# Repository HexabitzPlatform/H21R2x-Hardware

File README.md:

# H21R20-Hardware
Hexabitz ESP32-C3 WiFi+BLE Module Hardware Design

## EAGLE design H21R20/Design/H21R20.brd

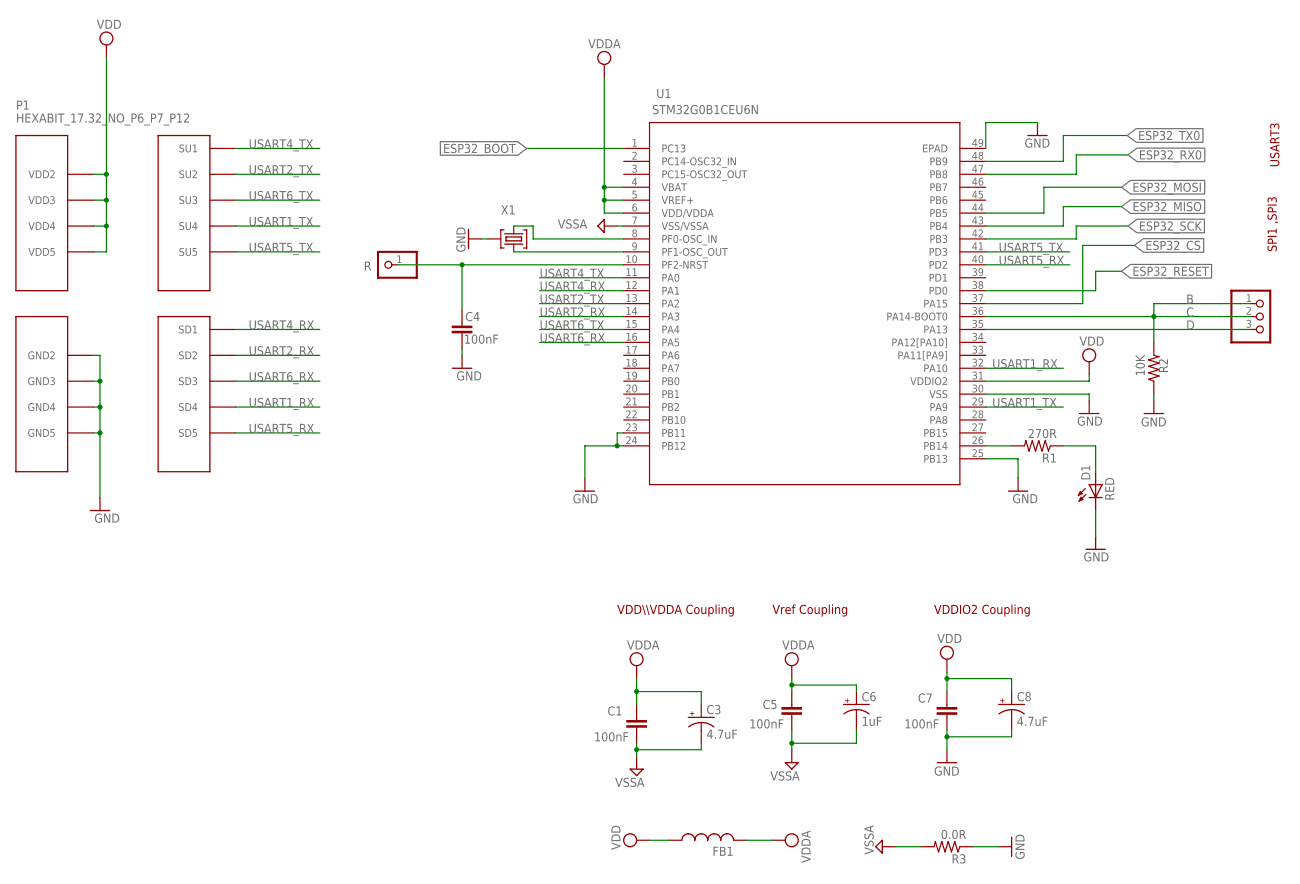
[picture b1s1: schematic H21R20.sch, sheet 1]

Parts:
C1, C5, C7: 100nF; C-0603; TOLERANCE 10%; VOLTAGE_RATING 16.0 V; MPN '0603YC104K4T2A
C3: 4.7uF; C-0805-POL; TOLERANCE 20%; VOLTAGE_RATING 10.0 V; MPN '10TPU4R7MSI
C4: 100nF; C-0603; TOLERANCE 10%; VOLTAGE_RATING 16.0 V; MPN 0603YC104K4T2A
C6: 1uF; C-0805-POL; TOLERANCE 20%; VOLTAGE_RATING 10.0 V; MPN 'CC0805KKX7R7BB105
C8: 4.7uF; C-0805-POL; TOLERANCE 10%; VOLTAGE_RATING 16.0 V; MPN '10TPU4R7MSI
D1: RED; VLMS1300-GS08
FB1: FB-TDK_MMZ1608Y300B; MPN MMZ1608Y300BTA00
JP1: PINHD-1X3; 1X03
P1: HEXABIT_17.32_NO_P6_P7_P12
R: PINHD-1X1; 1X01
R1: 270R; R-0603; MPN 'ERJ-3GEYJ271V
R2: 10K; R-0603; MPN '060300J0103T5E
R3: 0.0R; R-0603; MPN RC0603JR-070RL
U1: STM32G0B1CEU6N; HEXABITZ_ICS_QFN_B1CEU6_STM-L
X1: 8MHZ; XTALL_CSTCE8M00G52; MPN CSTNE8M00G550000R0

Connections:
C: JP1.1, JP1.2, R2.2, U1.36 (PA14-BOOT0)
D: JP1.3, U1.35 (PA13)
ESP32_BOOT: U1.1 (PC13); also elsewhere on the board
ESP32_CS: U1.37 (PA15); also elsewhere on the board
ESP32_MISO: U1.43 (PB4); also elsewhere on the board
ESP32_MOSI: U1.44 (PB5); also elsewhere on the board
ESP32_RESET: U1.38 (PD0); also elsewhere on the board
ESP32_RX0: U1.47 (PB8); also elsewhere on the board
ESP32_SCK: U1.42 (PB3); also elsewhere on the board
ESP32_TX0: U1.48 (PB9); also elsewhere on the board
GND: C4.1, C7.1, C8.2 (-), D1.C, P1.PAD_PD8 (GND2), P1.PAD_PD9 (GND3), P1.PAD_PD10 (GND4), P1.PAD_PD11 (GND5), R2.1, R3.1, U1.23 (PB11), U1.24 (PB12), U1.25 (PB13), U1.30 (VSS), U1.49 (EPAD), X1.P$2 (2); also elsewhere on the board
unnamed: U1.8 (PF0-OSC_IN), X1.P$1 (1)
unnamed: U1.9 (PF1-OSC_OUT), X1.P$3 (3)
unnamed: C4.2, R.1, U1.10 (PF2-NRST)
unnamed: R1.2, U1.26 (PB14)
unnamed: D1.A, R1.1
USART1_RX: P1.PAD_PD4 (SD4), U1.32 (PA10)
USART1_TX: P1.PAD_PU4 (SU4), U1.29 (PA9)
USART2_RX: P1.PAD_PD2 (SD2), U1.14 (PA3)
USART2_TX: P1.PAD_PU2 (SU2), U1.13 (PA2)
USART4_RX: P1.PAD_PD1 (SD1), U1.12 (PA1)
USART4_TX: P1.PAD_PU1 (SU1), U1.11 (PA0)
USART5_RX: P1.PAD_PD5 (SD5), U1.40 (PD2)
USART5_TX: P1.PAD_PU5 (SU5), U1.41 (PD3)
USART6_RX: P1.PAD_PD3 (SD3), U1.16 (PA5)
USART6_TX: P1.PAD_PU3 (SU3), U1.15 (PA4)
VDD: C7.2, C8.1 (+), FB1.1, P1.PAD_PU8 (VDD2), P1.PAD_PU9 (VDD3), P1.PAD_PU10 (VDD4), P1.PAD_PU11 (VDD5), U1.31 (VDDIO2); also elsewhere on the board
VDDA: C1.2, C3.1 (+), C5.2, C6.1 (+), FB1.2, U1.4 (VBAT), U1.5 (VREF+), U1.6 (VDD/VDDA)
VSSA: C1.1, C3.2 (-), C5.1, C6.2 (-), R3.2, U1.7 (VSS/VSSA)

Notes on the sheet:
VDDIO2 Coupling
VDD\\\VDDA Coupling
Vref Coupling
SPI1 ,SPI3
USART3

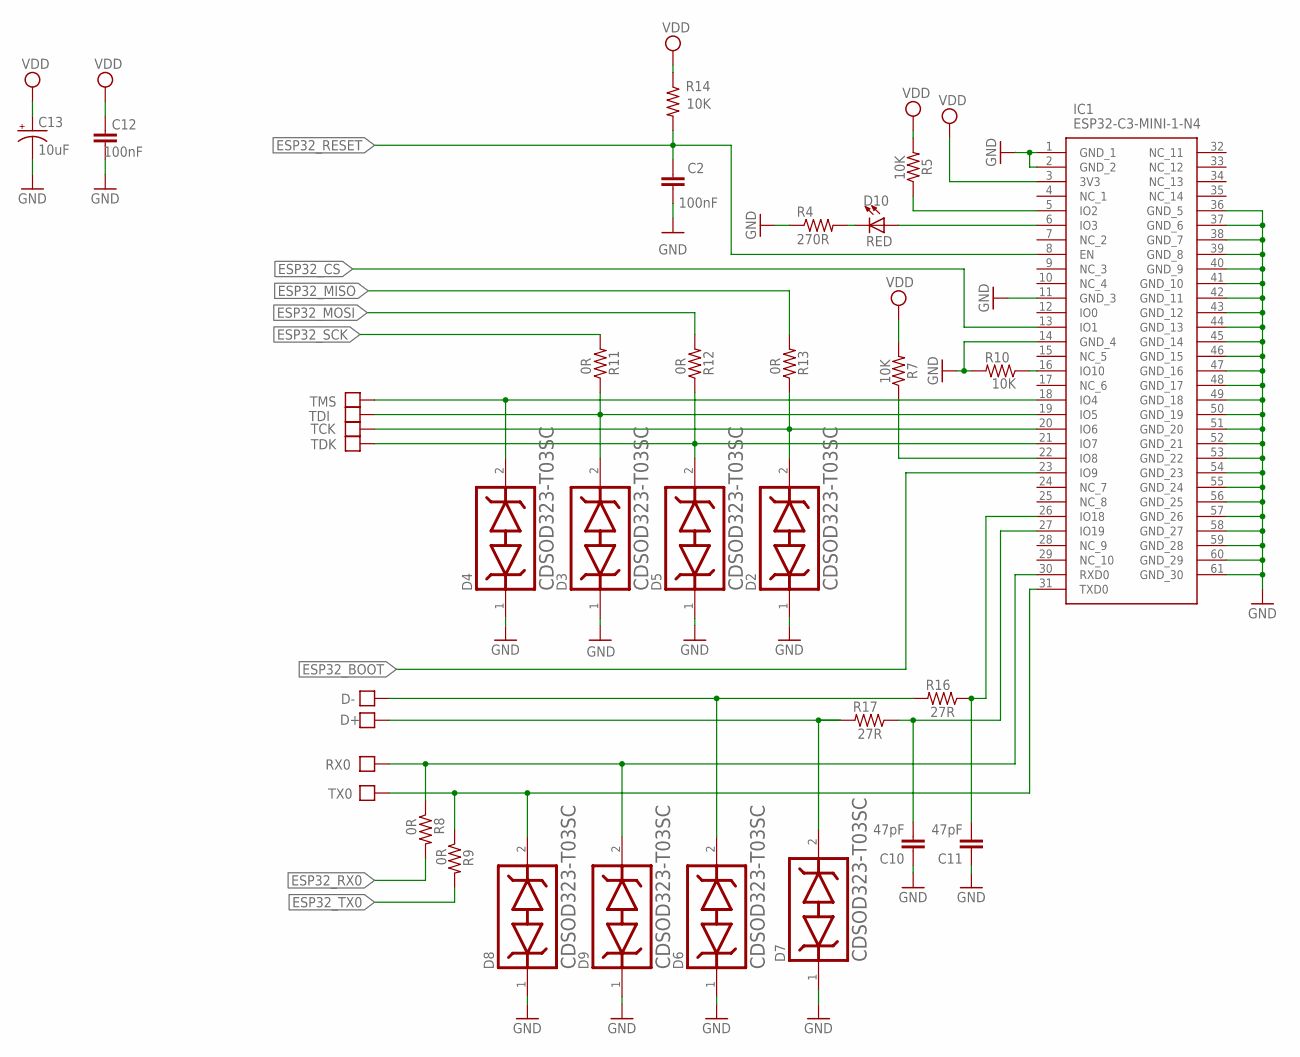
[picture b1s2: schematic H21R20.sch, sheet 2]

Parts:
C2, C12: 100nF; C-0603; TOLERANCE 10%; VOLTAGE_RATING 16.0 V; MPN '0603YC104K4T2A
C10, C11: 47pF; C-0603; TOLERANCE 10%; VOLTAGE_RATING 16.0 V; MPN '0603YC104K4T2A
C13: 10uF; C-1210-POL
D2, D3, D4, D5, D6, D7, D8, D9: BOURNS_CDSOD323-T03SCBOURNS_CDSOD323-T03SC_0_0; BOURNS_CDSOD323-T03SC_0
D10: RED; VLMS1300-GS08
D+: PAD4
D-: PAD4
IC1: ESP32-C3-MINI-1-N4; ESP32C3MINI1N4
R4: 270R; R-0603; MPN 'ERJ-3GEYJ271V
R5, R7, R10, R14: 10K; R-0603; MPN RC0603JR-070RL
R8, R9: 0R; R-0603; MPN RC0603JR-070RL
R11, R12, R13: 0R; R-0402; MPN RC0603JR-070RL
R16, R17: 27R; R-0603; MPN RC0603JR-070RL
RX0: PAD4
TCK: PAD4
TDI: PAD4
TDK: PAD4
TMS: PAD4
TX0: PAD4

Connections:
DATA_N: C11.2, IC1.26 (IO18), R16.1
DATA_P: C10.2, IC1.27 (IO19), R17.1
D_N: D6.2, D-.P$1, R16.2
D_P: D7.2, D+.P$1, R17.2
ESP32_BOOT: IC1.23 (IO9); also elsewhere on the board
ESP32_CS: IC1.13 (IO1); also elsewhere on the board
ESP32_MISO: R13.2; also elsewhere on the board
ESP32_MOSI: R12.2; also elsewhere on the board
ESP32_RESET: C2.2, IC1.8 (EN), R14.2; also elsewhere on the board
ESP32_RX0: R8.2; also elsewhere on the board
ESP32_SCK: R11.2; also elsewhere on the board
ESP32_TX0: R9.2; also elsewhere on the board
GND: C2.1, C10.1, C11.1, C12.1, C13.2 (-), D2.1, D3.1, D4.1, D5.1, D6.1, D7.1, D8.1, D9.1, IC1.1 (GND_1), IC1.2 (GND_2), IC1.11 (GND_3), IC1.14 (GND_4), IC1.36 (GND_5), IC1.37 (GND_6), IC1.38 (GND_7), IC1.39 (GND_8), IC1.40 (GND_9), IC1.41 (GND_10), IC1.42 (GND_11), IC1.43 (GND_12), IC1.44 (GND_13), IC1.45 (GND_14), IC1.46 (GND_15), IC1.47 (GND_16), IC1.48 (GND_17), IC1.49 (GND_18), IC1.50 (GND_19), IC1.51 (GND_20), IC1.52 (GND_21), IC1.53 (GND_22), IC1.54 (GND_23), IC1.55 (GND_24), IC1.56 (GND_25), IC1.57 (GND_26), IC1.58 (GND_27), IC1.59 (GND_28), IC1.60 (GND_29), IC1.61 (GND_30), R4.1, R10.2; also elsewhere on the board
unnamed: D4.2, IC1.18 (IO4), TMS.P$1
unnamed: IC1.22 (IO8), R7.1
unnamed: D10.C, R4.2
unnamed: D9.2, IC1.30 (RXD0), R8.1, RX0.P$1
unnamed: D8.2, IC1.31 (TXD0), R9.1, TX0.P$1
unnamed: IC1.16 (IO10), R10.1
unnamed: D2.2, IC1.20 (IO6), R13.1, TCK.P$1
unnamed: D5.2, IC1.21 (IO7), R12.1, TDK.P$1
unnamed: D10.A, IC1.6 (IO3)
unnamed: IC1.5 (IO2), R5.1
unnamed: D3.2, IC1.19 (IO5), R11.1, TDI.P$1
VDD: C12.2, C13.1 (+), IC1.3 (3V3), R5.2, R7.2, R14.1; also elsewhere on the board

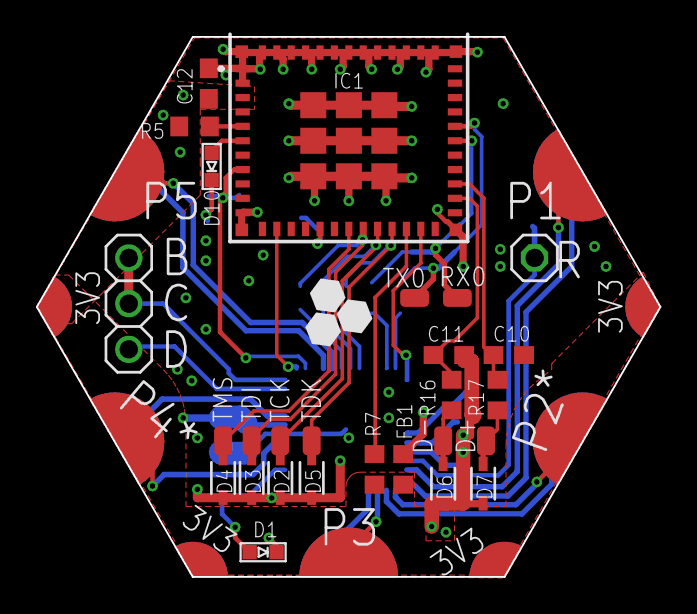
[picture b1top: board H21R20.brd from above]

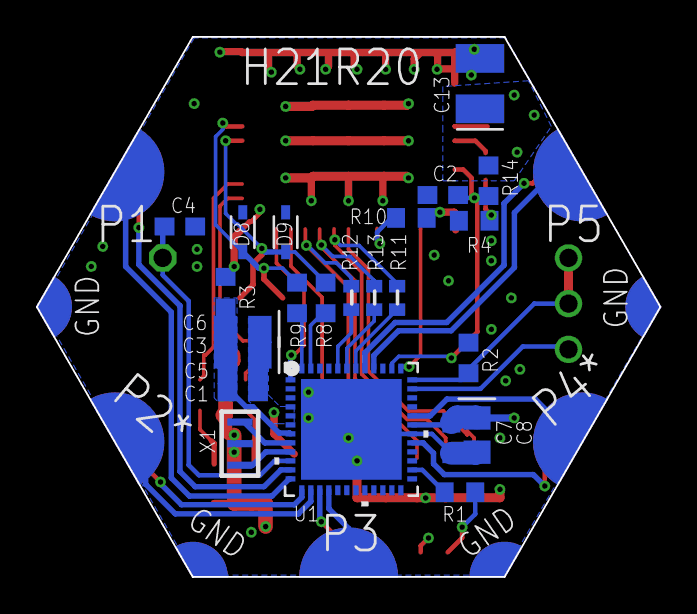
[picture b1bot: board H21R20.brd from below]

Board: 2 copper layers, 34.6 x 30.0 mm, 52 parts (24 on the bottom side), 44 nets.

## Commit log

2021-06-23 - schematic and PCB designes - BOM - output files - Documentation
2022-09-12 -Changing the MC to STM32G0B1CEU6N -Changing the design of the hardware of the ESP32 circuit and the way it is connected to the MC,and adding test points to help with programming and debugging
2022-09-21 -Changing some issues in the design to improve the performance
2022-10-30 -Changing the placement of the ESP32
2023-02-13 -Correcting some documentaion issues
2023-11-16 -Improve the layout design -Change the jumber resistors footprint to 0402
2023-11-16 -Correct some documentation issues
2023-11-26 -Doing some changes at the silkscreen layer level

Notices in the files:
parts and their libraries:
HEXABITZ_ICs: COPYRIGHT: Copyright (C) 2022 Ultra Librarian. All rights reserved.
